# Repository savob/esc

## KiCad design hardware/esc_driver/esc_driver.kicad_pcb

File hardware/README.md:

# ESC Hardware Files

Here are the files related to the hardware design. They are all from KiCad 7.0.10 at the oldest.

## Projects

- `esc_vX` are different versions of the ESC
- `driver_ic_adapter` is a board I designed to act as an adapter so I could seat an IRS2334S chip on the footprint for a FAN7x88 chip
- `esc_driver` is a board just meant to hold the power stage of the ESC so one can connect it to different control circuits

## Other Files and Folders

- `esc.3dshapes` contains 3D models for custom footpints
- `esc.pretty` holds all the custom footprints needed by the ESC project
- `schematics` has the schematics in PDF (colour and B/W) and SVG (just colour) formats
- `esc_part.kicad_sym` holds the custom symbols used in the ESC project
- `small_title_block.kicad_wks` has the worksheet template with a more compact titleblock

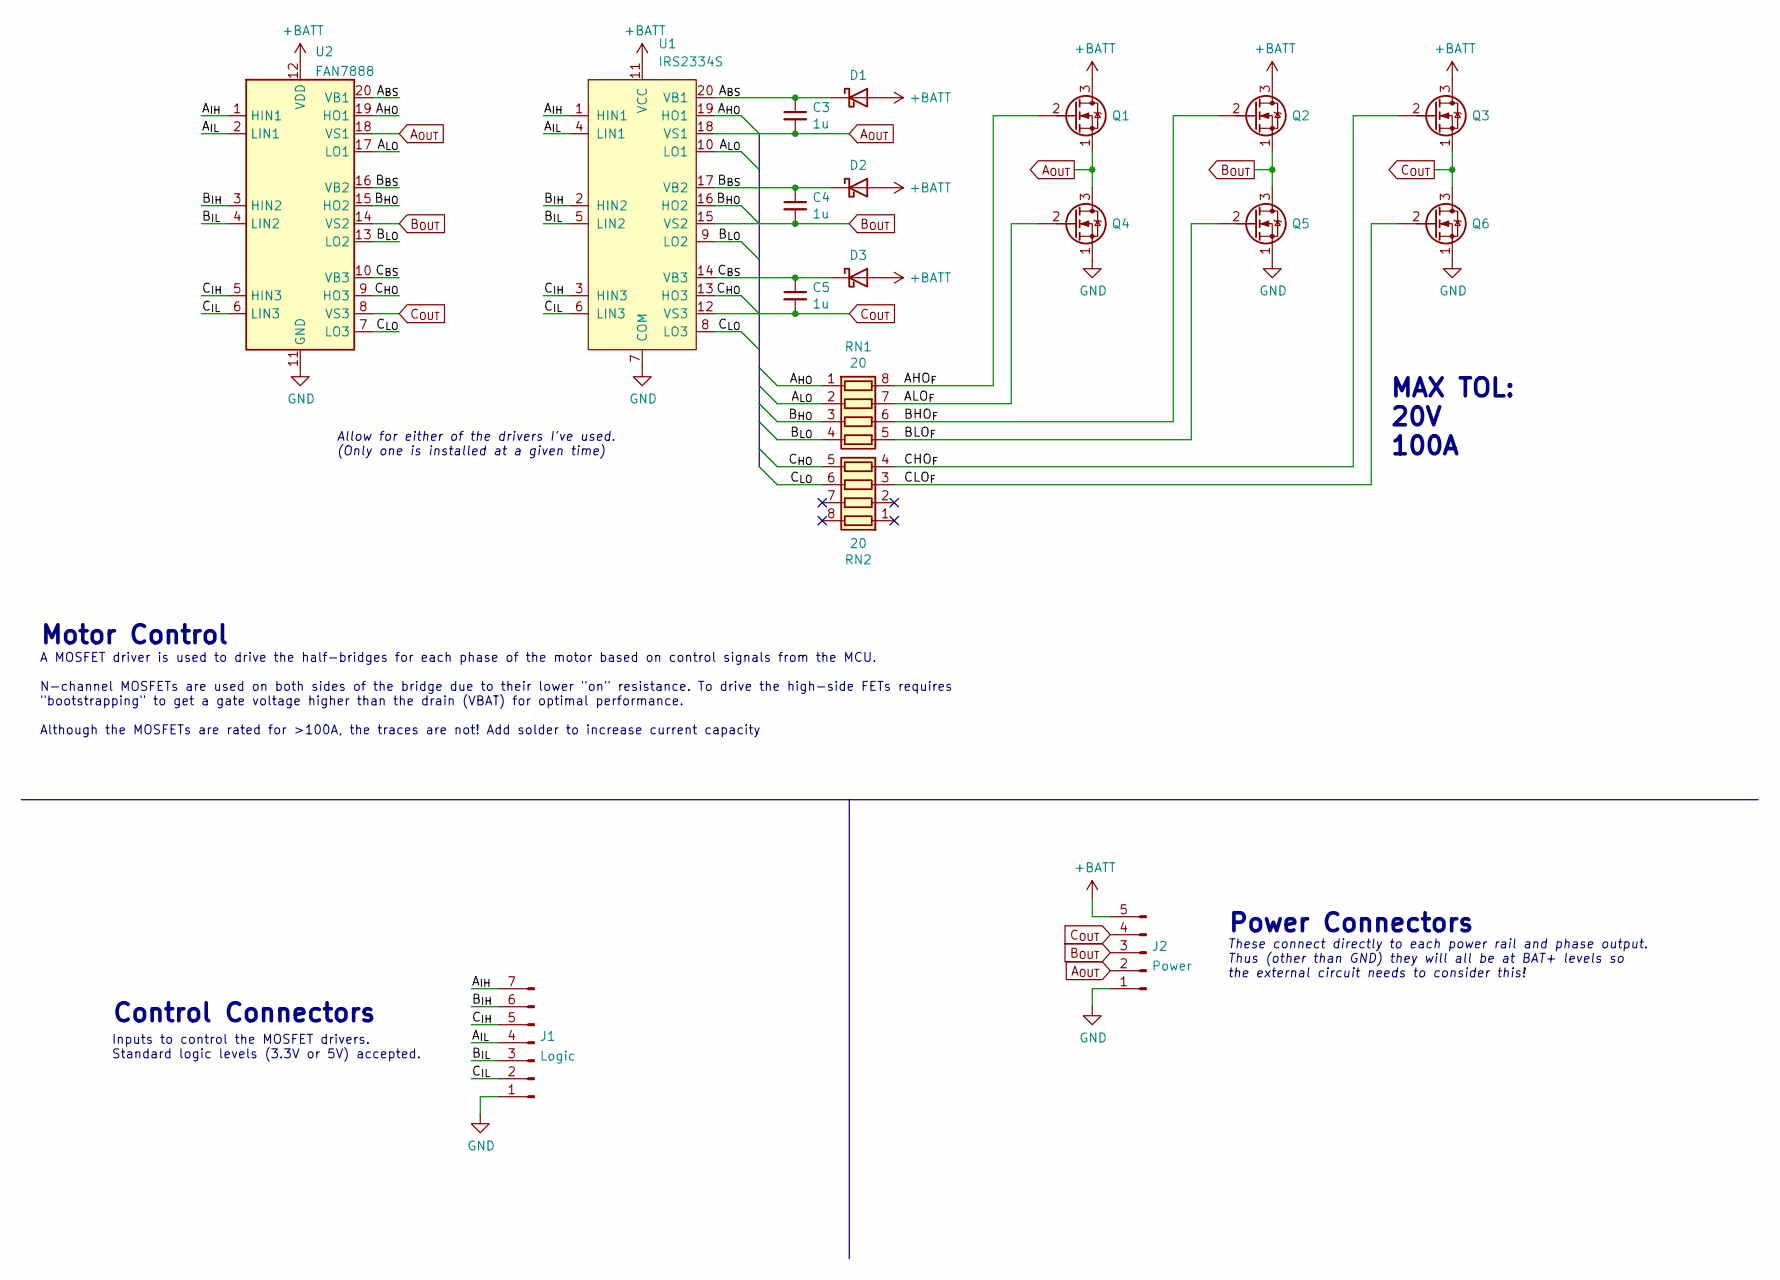
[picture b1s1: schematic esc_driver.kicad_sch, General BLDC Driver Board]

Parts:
C3, C4, C5: 1u; C_0603_1608Metric
D1, D2, D3: DSS15UTR; D_SOD-123F
J1: Logic; PinHeader_1x07_P2.54mm_Vertical
J2: Power; PinHeader_1x05_P2.54mm_Vertical
Q1, Q2, Q3, Q4, Q5, Q6: TPN2R903PL; TPN2R903PLL1Q
RN1, RN2: 20; R_Array_Convex_4x0603
U1: IRS2334S; SOIC-20W_7.5x12.8mm_P1.27mm
U2: FAN7888; SOIC-20W_7.5x12.8mm_P1.27mm

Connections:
+BATT: D1.2 (A), D2.2 (A), D3.2 (A), J2.5, Q1.3 (D), Q2.3 (D), Q3.3 (D), U1.11 (VCC), U2.12 (VDD)
/AHO_{F}: Q1.2 (G), RN1.8 (R1.2)
/ALO_{F}: Q4.2 (G), RN1.7 (R2.2)
/A_{BS}: C3.1, D1.1 (K), U1.20 (VB1), U2.20 (VB1)
/A_{HO}: RN1.1 (R1.1), U1.19 (HO1), U2.19 (HO1)
/A_{IH}: J1.7, U1.1 (HIN1), U2.1 (HIN1)
/A_{IL}: J1.4, U1.4 (LIN1), U2.2 (LIN1)
/A_{LO}: RN1.2 (R2.1), U1.10 (LO1), U2.17 (LO1)
/BHO_{F}: Q2.2 (G), RN1.6 (R3.2)
/BLO_{F}: Q5.2 (G), RN1.5 (R4.2)
/B_{BS}: C4.1, D2.1 (K), U1.17 (VB2), U2.16 (VB2)
/B_{HO}: RN1.3 (R3.1), U1.16 (HO2), U2.15 (HO2)
/B_{IH}: J1.6, U1.2 (HIN2), U2.3 (HIN2)
/B_{IL}: J1.3, U1.5 (LIN2), U2.4 (LIN2)
/B_{LO}: RN1.4 (R4.1), U1.9 (LO2), U2.13 (LO2)
/CHO_{F}: Q3.2 (G), RN2.4 (R4.1)
/CLO_{F}: Q6.2 (G), RN2.3 (R3.1)
/C_{BS}: C5.1, D3.1 (K), U1.14 (VB3), U2.10 (VB3)
/C_{HO}: RN2.5 (R4.2), U1.13 (HO3), U2.9 (HO3)
/C_{IH}: J1.5, U1.3 (HIN3), U2.5 (HIN3)
/C_{IL}: J1.2, U1.6 (LIN3), U2.6 (LIN3)
/C_{LO}: RN2.6 (R3.2), U1.8 (LO3), U2.7 (LO3)
A_{OUT}: C3.2, J2.2, Q1.1 (S), Q4.3 (D), U1.18 (VS1), U2.18 (VS1)
B_{OUT}: C4.2, J2.3, Q2.1 (S), Q5.3 (D), U1.15 (VS2), U2.14 (VS2)
C_{OUT}: C5.2, J2.4, Q3.1 (S), Q6.3 (D), U1.12 (VS3), U2.8 (VS3)
GND: J1.1, J2.1, Q4.1 (S), Q5.1 (S), Q6.1 (S), U1.7 (COM), U2.11 (GND)

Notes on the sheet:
A MOSFET driver is used to drive the half-bridges for each phase of the motor based on control signals from the MCU. N-channel MOSFETs are used on both sides of the bridge due to their lower "on" resistance. To drive the high-side FETs requires "bootstrapping" to get a gate voltage higher than the 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
These connect directly to each power rail and phase output. Thus (other than GND) they will all be at BAT+ levels so the external circuit needs to consider this!
Motor Control
Allow for either of the drivers I've used. (Only one is installed at a given time)
Power Connectors
MAX TOL: 20V 100A
Inputs to control the MOSFET drivers. Standard logic levels (3.3V or 5V) accepted.
Control Connectors

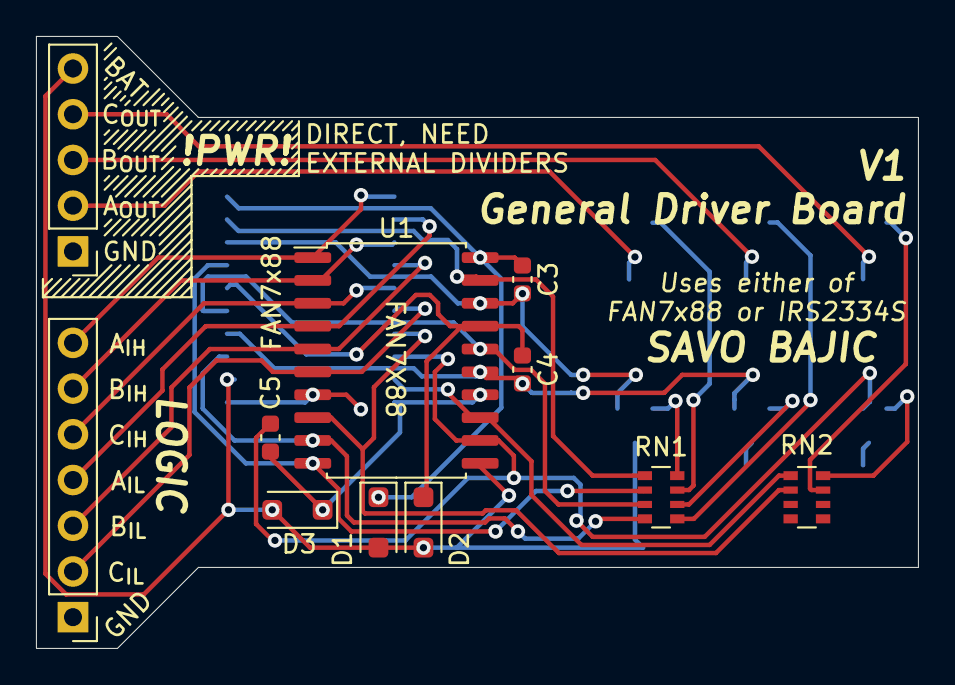
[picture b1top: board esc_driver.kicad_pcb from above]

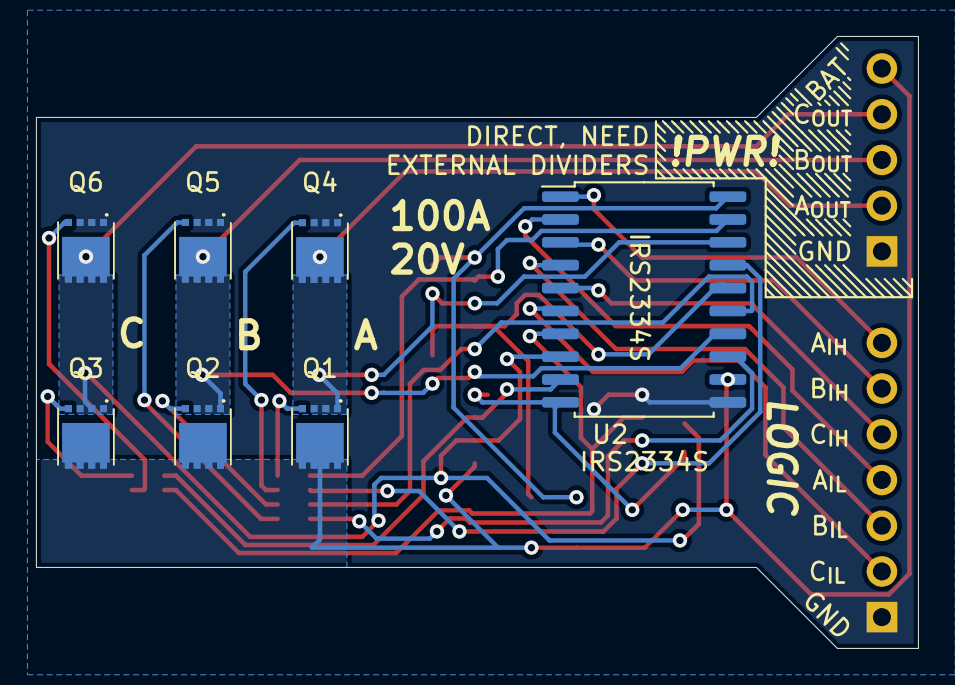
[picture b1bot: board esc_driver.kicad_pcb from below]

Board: 2 copper layers, 49.0 x 34.0 mm, 18 parts (7 on the bottom side), 26 nets.

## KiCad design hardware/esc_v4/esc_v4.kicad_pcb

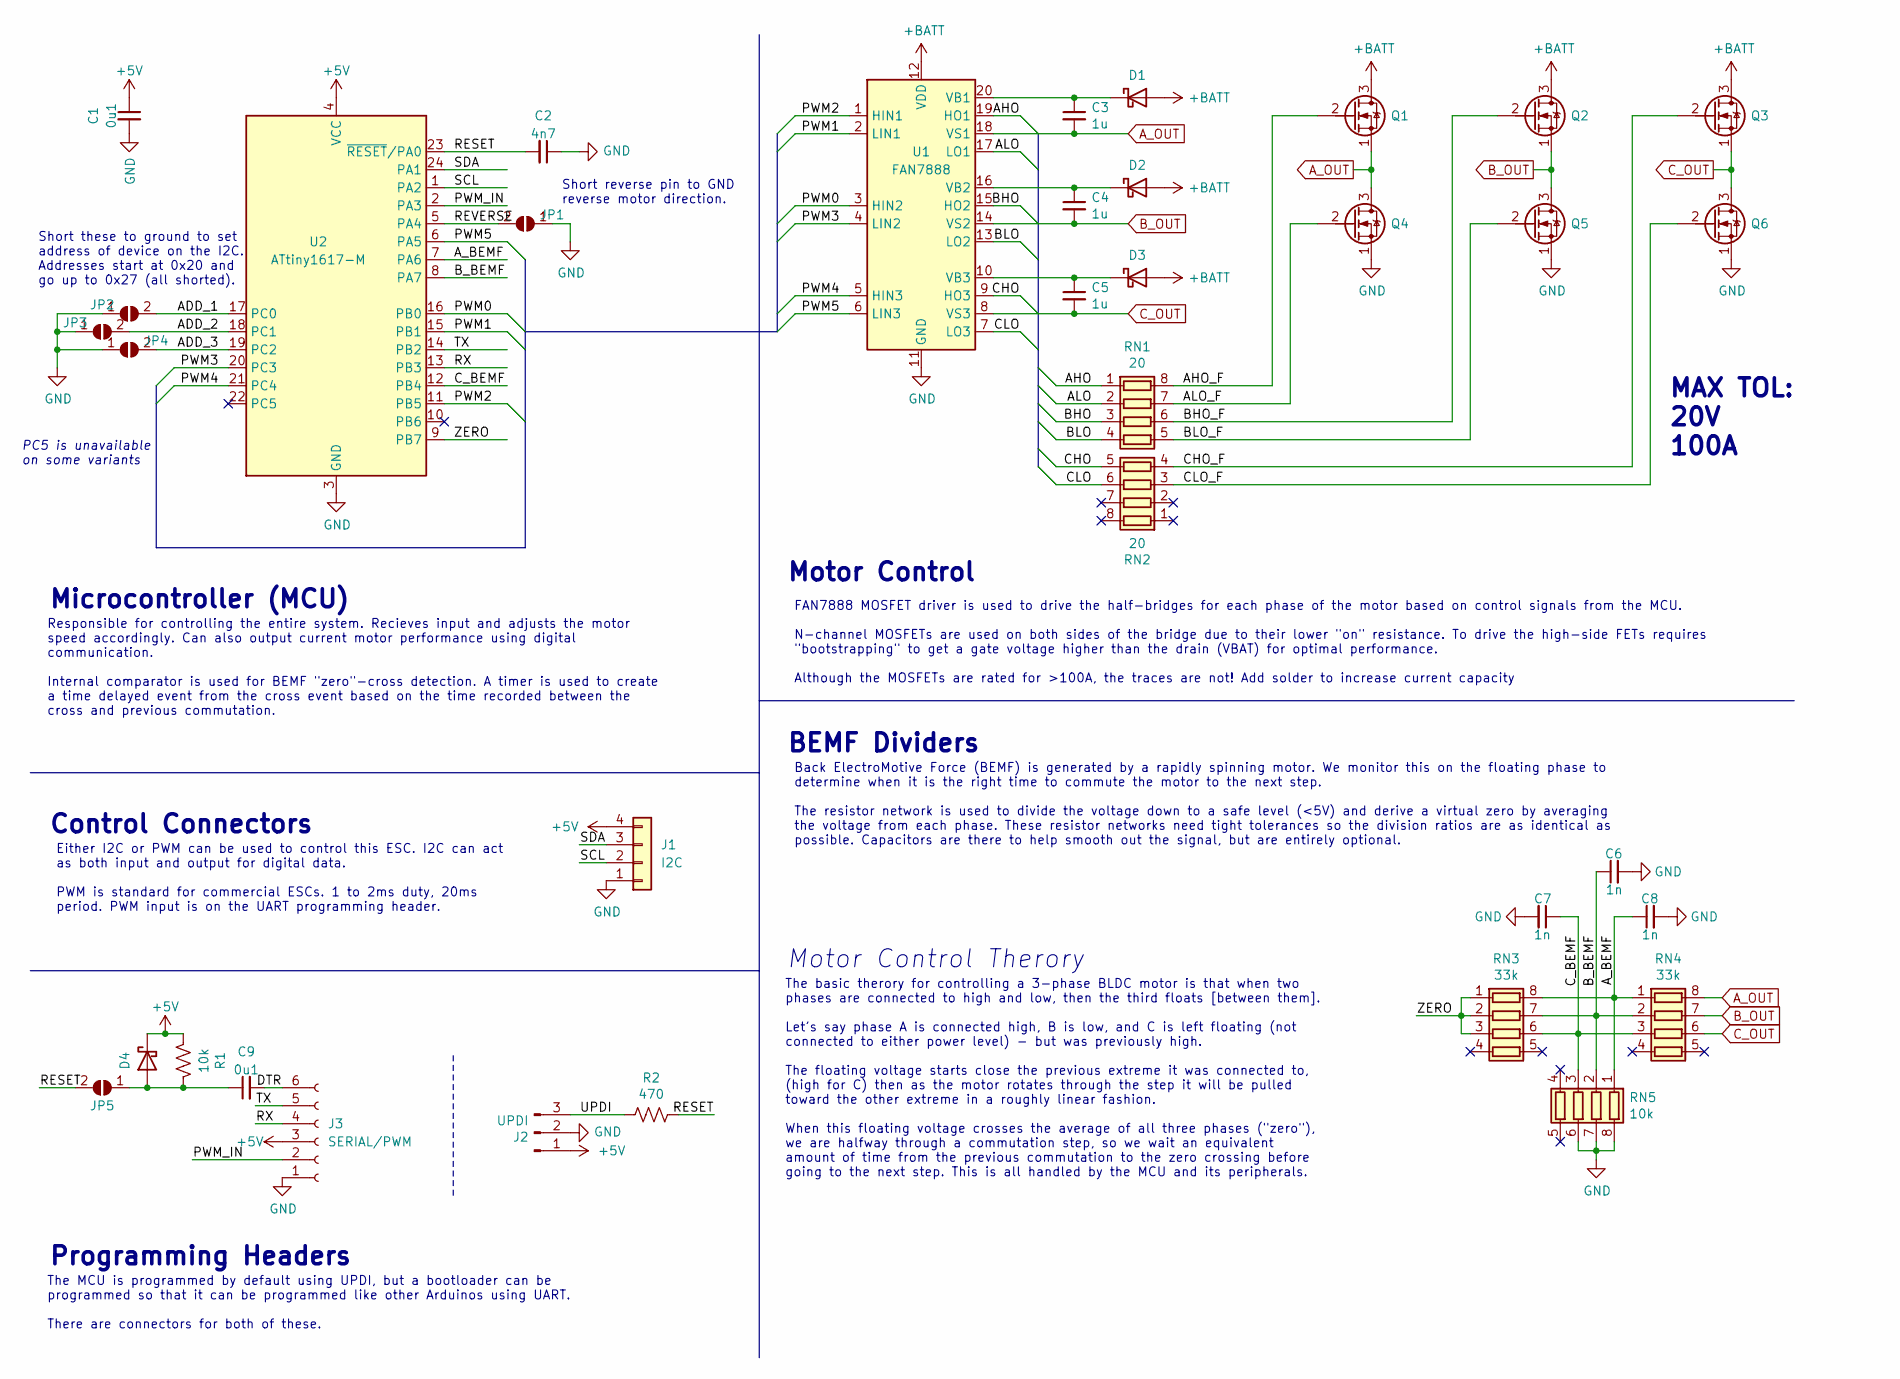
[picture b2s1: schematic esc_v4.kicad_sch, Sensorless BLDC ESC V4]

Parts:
C1, C9: 0u1; C_0402_1005Metric
C2: 4n7; C_0402_1005Metric
C3, C4, C5: 1u; C_0603_1608Metric
C6, C7, C8: 1n; C_0402_1005Metric
D1, D2, D3, D4: DSS15UTR; D_SOD-123F
J1: I2C; PinSocket_1x04_P2.54mm_Vertical
J2: UPDI; PinHeader_1x03_P2.54mm_Horizontal
J3: SERIAL/PWM; PinSocket_1x06_P2.54mm_Vertical
JP1, JP2, JP3, JP4: SolderJumper_2_Open; SolderJumper-2_P1.3mm_Open_TrianglePad1.0x1.5mm
JP5: SolderJumper_2_Open; SolderJumper-2_P1.3mm_Open_RoundedPad1.0x1.5mm
Q1, Q2, Q3, Q4, Q5, Q6: TPN2R903PL; TPN2R903PLL1Q
R1: 10k; R_0603_1608Metric
R2: 470; R_0603_1608Metric
RN1, RN2: 20; R_Array_Convex_4x0603
RN3, RN4: 33k; R_Array_Convex_4x0603
RN5: 10k; R_Cat16-4
U1: FAN7888; SOIC-20W_7.5x12.8mm_P1.27mm
U2: ATtiny1617-M; QFN-24-1EP_4x4mm_P0.5mm_EP2.6x2.6mm

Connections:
+5V: C1.1, D4.1 (K), J1.4, J2.1, J3.3, R1.1, U2.4 (VCC)
+BATT: D1.2 (A), D2.2 (A), D3.2 (A), Q1.3 (D), Q2.3 (D), Q3.3 (D), U1.12 (VDD)
/ADD_1: JP2.2 (B), U2.17 (PC0)
/ADD_2: JP3.2 (B), U2.18 (PC1)
/ADD_3: JP4.2 (B), U2.19 (PC2)
/AHO: RN1.1 (R1.1), U1.19 (HO1)
/AHO_F: Q1.2 (G), RN1.8 (R1.2)
/ALO: RN1.2 (R2.1), U1.17 (LO1)
/ALO_F: Q4.2 (G), RN1.7 (R2.2)
/A_BEMF: C8.1, RN3.8 (R1.2), RN4.1 (R1.1), RN5.1 (R1.1), U2.7 (PA6)
/BHO: RN1.3 (R3.1), U1.15 (HO2)
/BHO_F: Q2.2 (G), RN1.6 (R3.2)
/BLO: RN1.4 (R4.1), U1.13 (LO2)
/BLO_F: Q5.2 (G), RN1.5 (R4.2)
/B_BEMF: C6.1, RN3.7 (R2.2), RN4.2 (R2.1), RN5.2 (R2.1), U2.8 (PA7)
/CHO: RN2.5 (R4.2), U1.9 (HO3)
/CHO_F: Q3.2 (G), RN2.4 (R4.1)
/CLO: RN2.6 (R3.2), U1.7 (LO3)
/CLO_F: Q6.2 (G), RN2.3 (R3.1)
/C_BEMF: C7.1, RN3.6 (R3.2), RN4.3 (R3.1), RN5.3 (R3.1), U2.12 (PB4)
/DTR: C9.2, J3.6
/PWM0: U1.3 (HIN2), U2.16 (PB0)
/PWM1: U1.2 (LIN1), U2.15 (PB1)
/PWM2: U1.1 (HIN1), U2.11 (PB5)
/PWM3: U1.4 (LIN2), U2.20 (PC3)
/PWM4: U1.5 (HIN3), U2.21 (PC4)
/PWM5: U1.6 (LIN3), U2.6 (PA5)
/PWM_IN: J3.2, U2.2 (PA3)
/RESET: C2.2, JP5.2 (B), R2.1, U2.23 (~RESET/PA0)
/REVERSE: JP1.2 (B), U2.5 (PA4)
/RX: J3.4, U2.13 (PB3)
/SCL: J1.2, U2.1 (PA2)
/SDA: J1.3, U2.24 (PA1)
/TX: J3.5, U2.14 (PB2)
/UPDI: J2.3, R2.2
/ZERO: RN3.1 (R1.1), RN3.2 (R2.1), RN3.3 (R3.1), U2.9 (PB7)
A_OUT: C3.2, Q1.1 (S), Q4.3 (D), RN4.8 (R1.2), U1.18 (VS1)
B_OUT: C4.2, Q2.1 (S), Q5.3 (D), RN4.7 (R2.2), U1.14 (VS2)
C_OUT: C5.2, Q3.1 (S), Q6.3 (D), RN4.6 (R3.2), U1.8 (VS3)
GND: C1.2, C2.1, C6.2, C7.2, C8.2, J1.1, J2.2, J3.1, JP1.1 (A), JP2.1 (A), JP3.1 (A), JP4.1 (A), Q4.1 (S), Q5.1 (S), Q6.1 (S), RN5.6 (R3.2), RN5.7 (R2.2), RN5.8 (R1.2), U1.11 (GND), U2.3 (GND), U2.25 (GND)
unnamed: C3.1, D1.1 (K), U1.20 (VB1)
unnamed: C4.1, D2.1 (K), U1.16 (VB2)
unnamed: C5.1, D3.1 (K), U1.10 (VB3)
unnamed: C9.1, D4.2 (A), JP5.1 (A), R1.2

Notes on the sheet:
Back ElectroMotive Force (BEMF) is generated by a rapidly spinning motor. We monitor this on the floating phase to determine when it is the right time to commute the motor to the next step. The resistor network is used to divide the voltage down to a safe level (<5V) and derive a virtual zero by av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
The basic therory for controlling a 3-phase BLDC motor is that when two phases are connected to high and low, then the third floats [between them]. Let's say phase A is connected high, B is low, and C is left floating (not connected to either power level) - but was previously high. The floating vol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
FAN7888 MOSFET driver is used to drive the half-bridges for each phase of the motor based on control signals from the MCU. N-channel MOSFETs are used on both sides of the bridge due to their lower "on" resistance. To drive the high-side FETs requires "bootstrapping" to get a gate voltage higher tha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
Either I2C or PWM can be used to control this ESC. I2C can act as both input and output for digital data. PWM is standard for commercial ESCs. 1 to 2ms duty, 20ms period. PWM input is on the UART programming header.
The MCU is programmed by default using UPDI, but a bootloader can be programmed so that it can be programmed like other Arduinos using UART. There are connectors for both of these.
Responsible for controlling the entire system. Recieves input and adjusts the motor speed accordingly. Can also output current motor performance using digital communication. Internal comparator is used for BEMF "zero"-cross detection. A timer is used to create a time delayed event from the cross ev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
Short these to ground to set address of device on the I2C. Addresses start at 0x20 and go up to 0x27 (all shorted).
Microcontroller (MCU)
MAX TOL: 20V 100A
Motor Control Therory
PC5 is unavailable on some variants
Control Connectors
Programming Headers
Short reverse pin to GND reverse motor direction.
Motor Control
BEMF Dividers

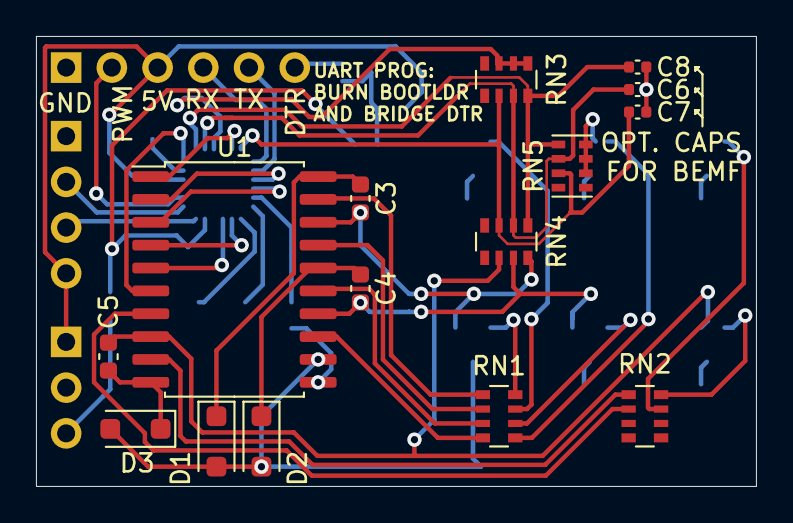
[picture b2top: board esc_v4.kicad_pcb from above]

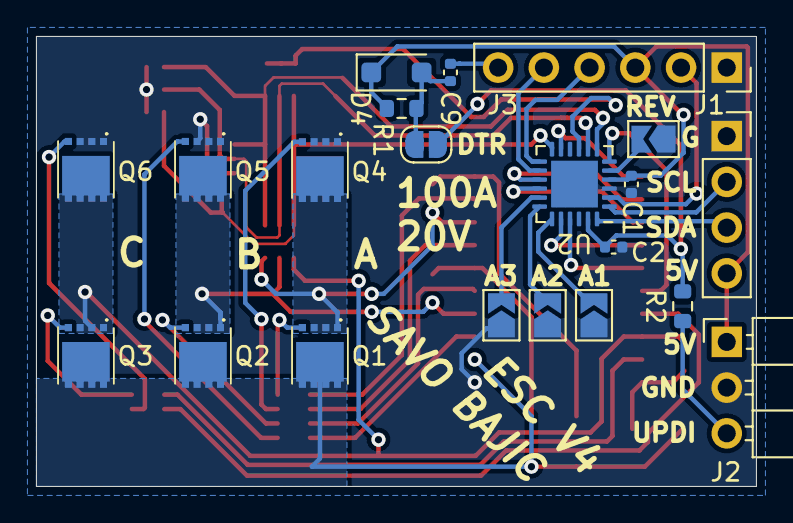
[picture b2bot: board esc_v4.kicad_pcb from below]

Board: 2 copper layers, 40.0 x 25.0 mm, 36 parts (21 on the bottom side), 44 nets.

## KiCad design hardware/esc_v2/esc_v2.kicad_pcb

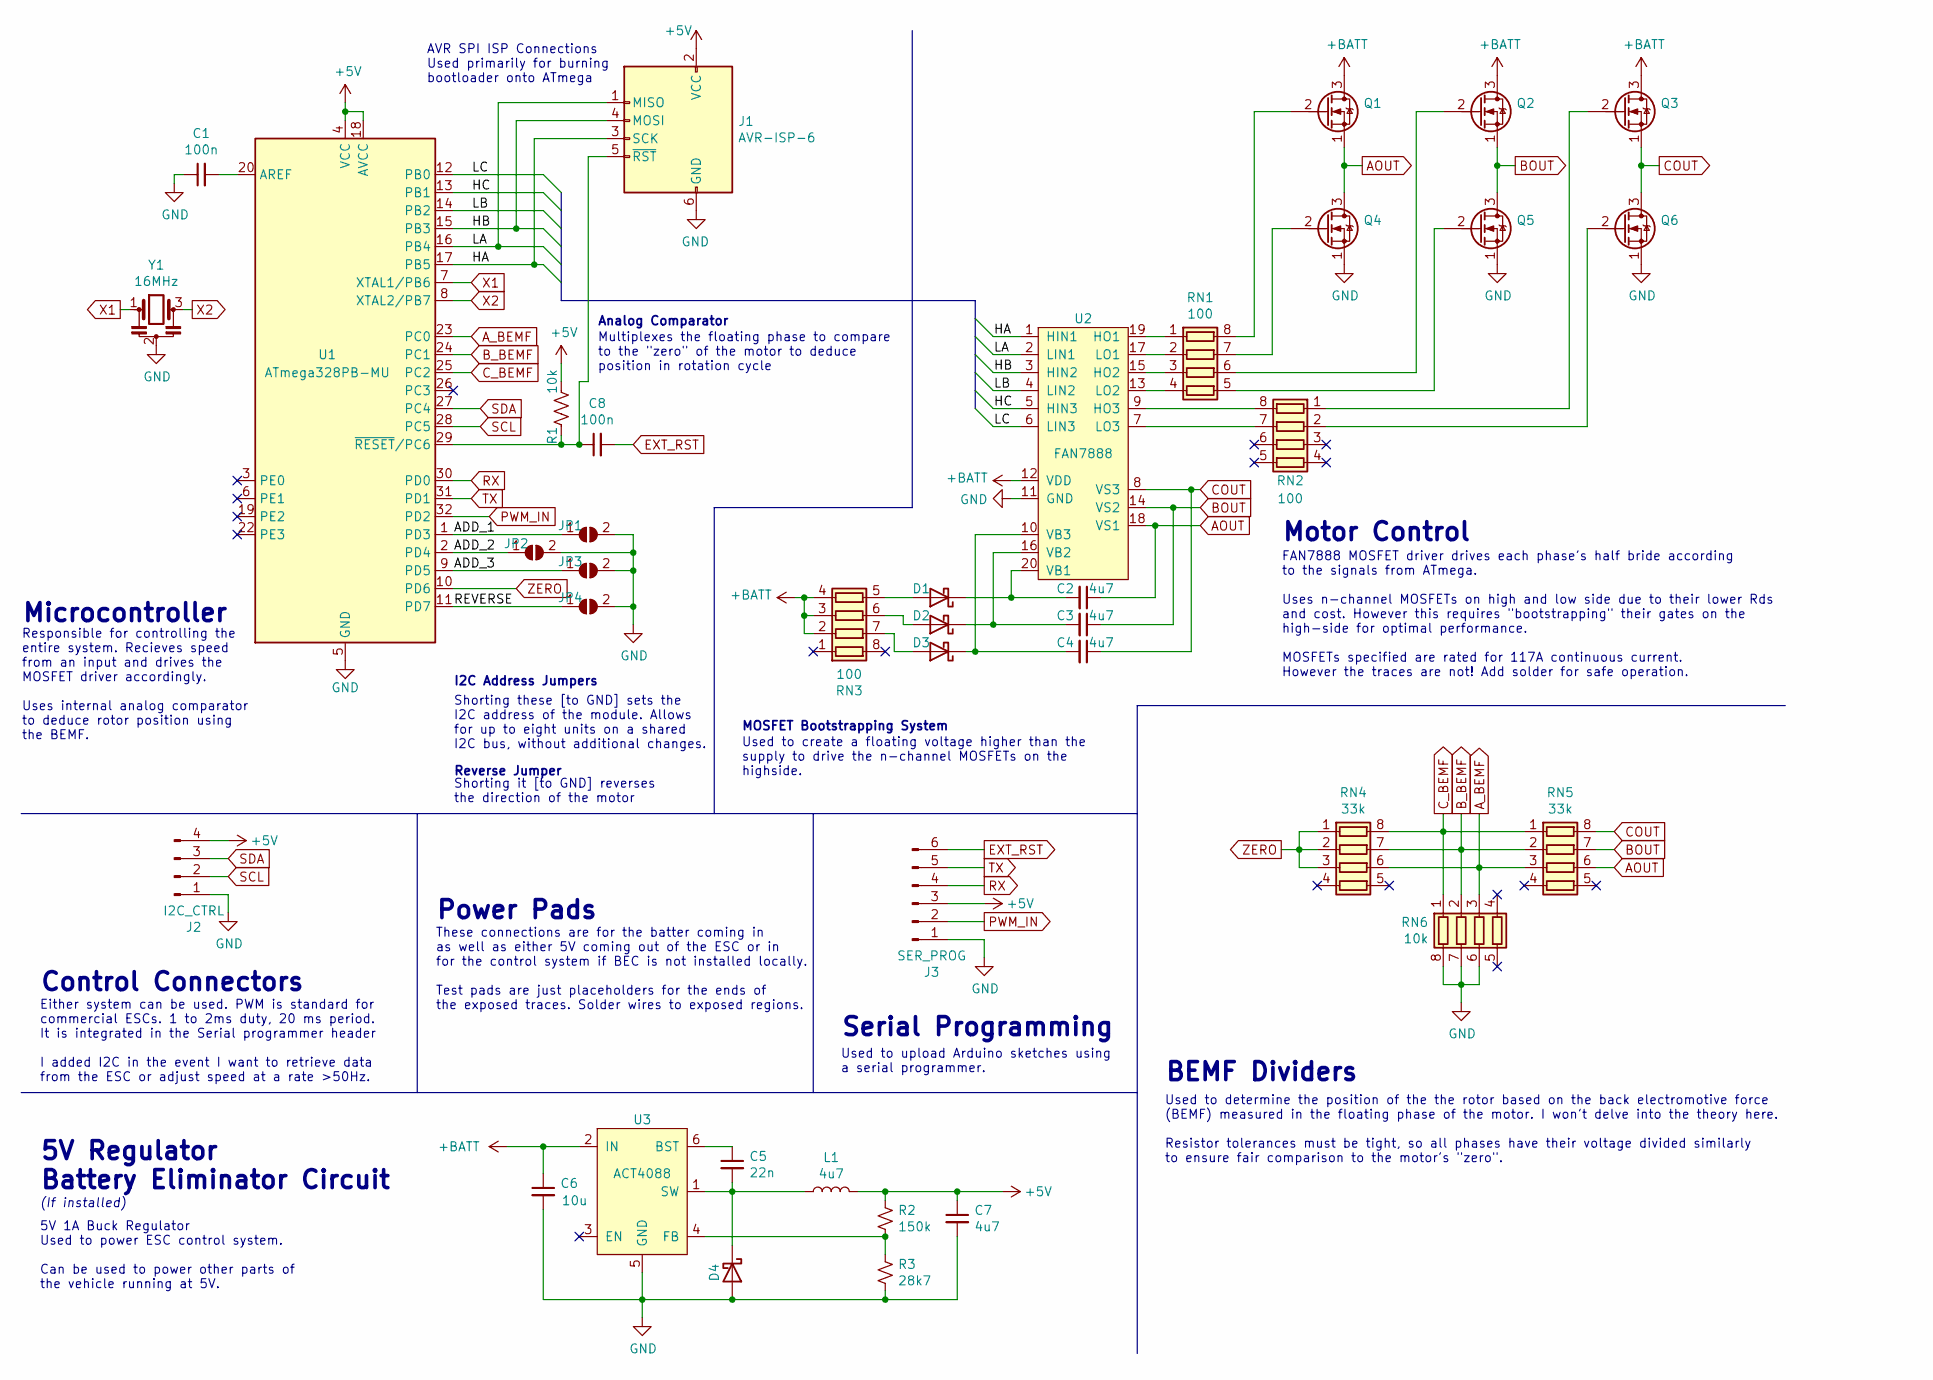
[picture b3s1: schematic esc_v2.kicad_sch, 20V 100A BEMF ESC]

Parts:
C1, C8: 100n; C_0402_1005Metric
C2, C3, C4, C7: 4u7; C_0805_2012Metric
C5: 22n; C_0402_1005Metric
C6: 10u; C_0805_2012Metric
D1, D2, D3, D4: 0v8; D_SOD-323
J1: AVR-ISP-6; PinHeader_2x03_P2.54mm_Vertical_SMD
J2: I2C_CTRL; PinHeader_1x04_P2.54mm_Vertical
J3: SER_PROG; PinSocket_1x06_P2.54mm_Vertical
JP1: A1; SolderJumper-2_P1.3mm_Open_TrianglePad1.0x1.5mm
JP2: A2; SolderJumper-2_P1.3mm_Open_TrianglePad1.0x1.5mm
JP3: A3; SolderJumper-2_P1.3mm_Open_TrianglePad1.0x1.5mm
JP4: REV; SolderJumper-2_P1.3mm_Open_TrianglePad1.0x1.5mm
L1: 4u7; L_Taiyo-Yuden_NR-30xx
Q1, Q2, Q3, Q4, Q5, Q6: Q_NMOS_SGD; TPN2R903PLL1Q
R1: 10k; R_0402_1005Metric
R2: 150k; R_0402_1005Metric
R3: 28k7; R_0402_1005Metric
RN1, RN2, RN3: 100; R_Array_Convex_4x0402
RN4, RN5: 33k; R_Array_Convex_4x0402
RN6: 10k; R_Array_Convex_4x0402
U1: ATmega328PB-MU; QFN-32-1EP_5x5mm_P0.5mm_EP3.1x3.1mm
U2: FAN7888; SOIC-20W_7.5x12.8mm_P1.27mm
U3: ACT4088; SOT-23-6
Y1: 16MHz; Resonator_SMD_muRata_CSTxExxV-3Pin_3.0x1.1mm

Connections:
+5V: C7.1, J1.2 (VCC), J2.4, J3.3, L1.2, R1.1, R2.2, U1.4 (VCC), U1.18 (AVCC)
+BATT: C6.1, Q1.3 (D), Q2.3 (D), Q3.3 (D), RN3.2 (R2.1), RN3.3 (R3.1), RN3.4 (R4.1), U2.12 (VDD), U3.2 (IN)
/ADD_1: JP1.1 (A), U1.1 (PD3)
/ADD_2: JP2.1 (A), U1.2 (PD4)
/ADD_3: JP3.1 (A), U1.9 (PD5)
/HA: J1.3 (SCK), U1.17 (PB5), U2.1 (HIN1)
/HB: J1.4 (MOSI), U1.15 (PB3), U2.3 (HIN2)
/HC: U1.13 (PB1), U2.5 (HIN3)
/LA: J1.1 (MISO), U1.16 (PB4), U2.2 (LIN1)
/LB: U1.14 (PB2), U2.4 (LIN2)
/LC: U1.12 (PB0), U2.6 (LIN3)
/REVERSE: JP4.1 (A), U1.11 (PD7)
AOUT: C2.1, Q1.1 (S), Q4.3 (D), RN5.6 (R3.2), U2.18 (VS1)
A_BEMF: RN4.6 (R3.2), RN5.3 (R3.1), RN6.3 (R3.1), U1.23 (PC0)
BOUT: C3.1, Q2.1 (S), Q5.3 (D), RN5.7 (R2.2), U2.14 (VS2)
B_BEMF: RN4.7 (R2.2), RN5.2 (R2.1), RN6.2 (R2.1), U1.24 (PC1)
COUT: C4.1, Q3.1 (S), Q6.3 (D), RN5.8 (R1.2), U2.8 (VS3)
C_BEMF: RN4.8 (R1.2), RN5.1 (R1.1), RN6.1 (R1.1), U1.25 (PC2)
EXT_RST: C8.2, J3.6
GND: C1.1, C6.2, C7.2, D4.2 (A), J1.6 (GND), J2.1, J3.1, JP1.2 (B), JP2.2 (B), JP3.2 (B), JP4.2 (B), Q4.1 (S), Q5.1 (S), Q6.1 (S), R3.1, RN6.6 (R3.2), RN6.7 (R2.2), RN6.8 (R1.2), U1.5 (GND), U1.21 (GND), U1.33 (GND), U2.11 (GND), U3.5 (GND), Y1.2
unnamed: D1.2 (A), RN3.5 (R4.2)
unnamed: C2.2, D1.1 (K), U2.20 (VB1)
unnamed: D2.2 (A), RN3.6 (R3.2)
unnamed: C3.2, D2.1 (K), U2.16 (VB2)
unnamed: D3.2 (A), RN3.7 (R2.2)
unnamed: C4.2, D3.1 (K), U2.10 (VB3)
unnamed: C5.2, D4.1 (K), L1.1, U3.1 (SW)
unnamed: C8.1, J1.5 (~RST), R1.2, U1.29 (~RESET/PC6)
unnamed: Q1.2 (G), RN1.8 (R1.2)
unnamed: Q2.2 (G), RN1.6 (R3.2)
unnamed: Q3.2 (G), RN2.1 (R1.1)
unnamed: Q4.2 (G), RN1.7 (R2.2)
unnamed: Q5.2 (G), RN1.5 (R4.2)
unnamed: Q6.2 (G), RN2.2 (R2.1)
unnamed: RN1.1 (R1.1), U2.19 (HO1)
unnamed: RN1.2 (R2.1), U2.17 (LO1)
unnamed: RN1.3 (R3.1), U2.15 (HO2)
unnamed: RN1.4 (R4.1), U2.13 (LO2)
unnamed: RN2.8 (R1.2), U2.9 (HO3)
unnamed: RN2.7 (R2.2), U2.7 (LO3)
unnamed: C1.2, U1.20 (AREF)
unnamed: C5.1, U3.6 (BST)
unnamed: R2.1, R3.2, U3.4 (FB)
PWM_IN: J3.2, U1.32 (PD2)
RX: J3.4, U1.30 (PD0)
SCL: J2.2, U1.28 (PC5)
SDA: J2.3, U1.27 (PC4)
TX: J3.5, U1.31 (PD1)
X1: U1.7 (XTAL1/PB6), Y1.1
X2: U1.8 (XTAL2/PB7), Y1.3
ZERO: RN4.1 (R1.1), RN4.2 (R2.1), RN4.3 (R3.1), U1.10 (PD6)

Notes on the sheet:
Serial Programming
5V 1A Buck Regulator Used to power ESC control system. Can be used to power other parts of the vehicle running at 5V.
AVR SPI ISP Connections Used primarily for burning bootloader onto ATmega
BEMF Dividers
Analog Comparator
Used to upload Arduino sketches using a serial programmer.
Shorting it [to GND] reverses the direction of the motor
Reverse Jumper
Shorting these [to GND] sets the I2C address of the module. Allows for up to eight units on a shared I2C bus, without additional changes.
These connections are for the batter coming in as well as either 5V coming out of the ESC or in for the control system if BEC is not installed locally. Test pads are just placeholders for the ends of the exposed traces. Solder wires to exposed regions.
Responsible for controlling the entire system. Recieves speed from an input and drives the MOSFET driver accordingly. Uses internal analog comparator to deduce rotor position using the BEMF.
Used to determine the position of the the rotor based on the back electromotive force (BEMF) measured in the floating phase of the motor. I won't delve into the theory here. Resistor tolerances must be tight, so all phases have their voltage divided similarly to ensure fair comparison to the motor'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
Control Connectors
Microcontroller
(If installed)
FAN7888 MOSFET driver drives each phase's half bride according to the signals from ATmega. Uses n-channel MOSFETs on high and low side due to their lower Rds and cost. However this requires "bootstrapping" their gates on the high-side for optimal performance. MOSFETs specified are rated for 117A co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
Either system can be used. PWM is standard for commercial ESCs. 1 to 2ms duty, 20 ms period. It is integrated in the Serial programmer header I added I2C in the event I want to retrieve data from the ESC or adjust speed at a rate >50Hz.
Used to create a floating voltage higher than the supply to drive the n-channel MOSFETs on the highside.
Motor Control
5V Regulator Battery Eliminator Circuit
I2C Address Jumpers
MOSFET Bootstrapping System
Power Pads
Multiplexes the floating phase to compare to the "zero" of the motor to deduce position in rotation cycle

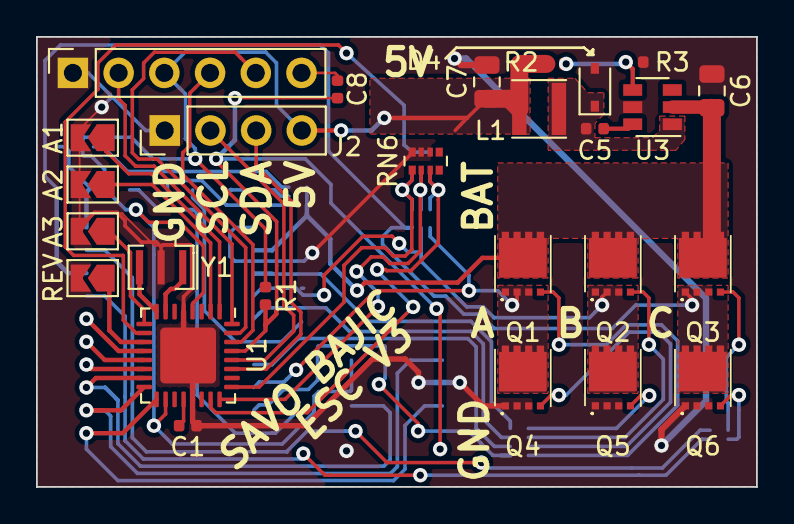
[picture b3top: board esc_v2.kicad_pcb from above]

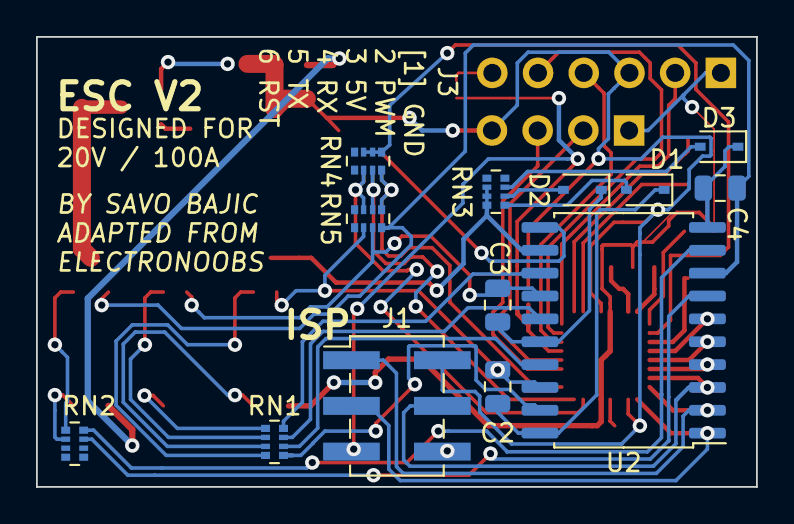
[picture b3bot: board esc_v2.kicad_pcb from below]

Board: 2 copper layers, 40.0 x 25.0 mm, 39 parts (13 on the bottom side), 51 nets.

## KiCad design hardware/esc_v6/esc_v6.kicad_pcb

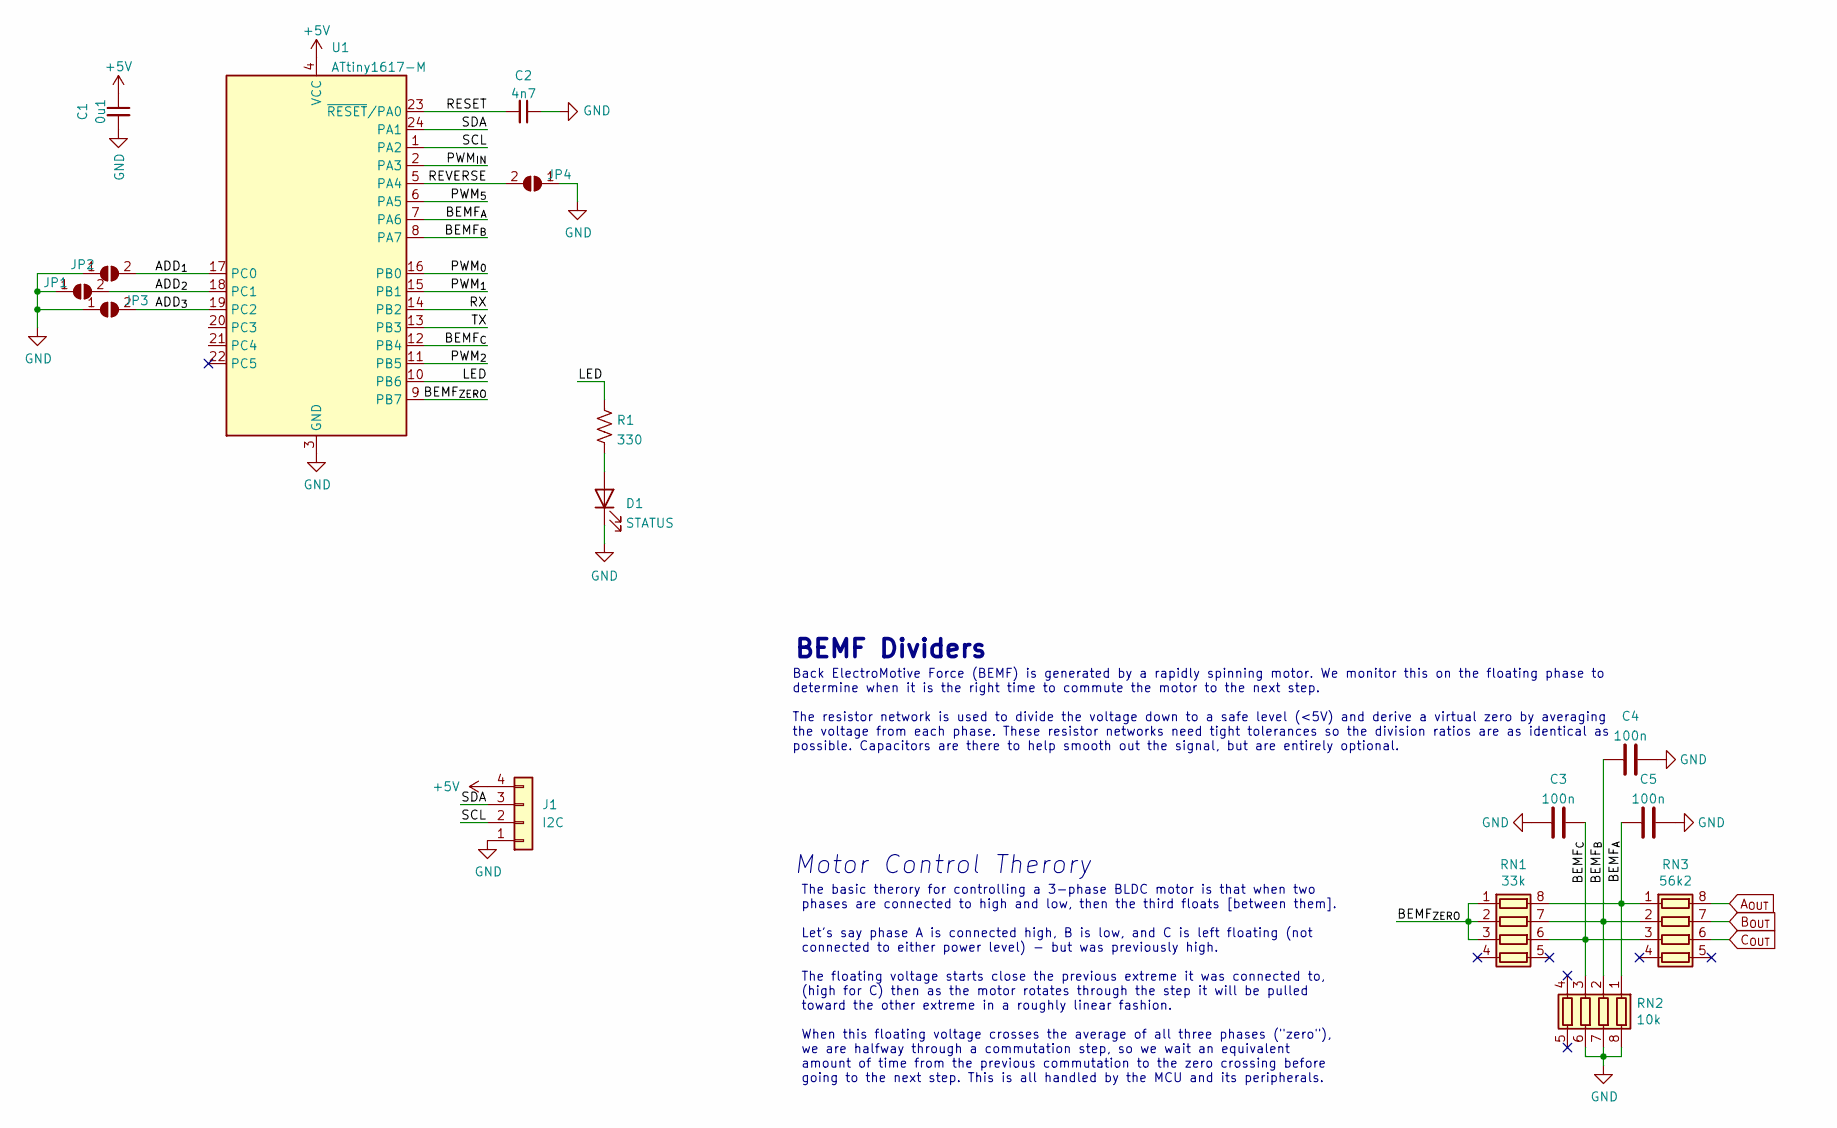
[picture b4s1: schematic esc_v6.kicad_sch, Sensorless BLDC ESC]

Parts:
C1: 0u1; C_0603_1608Metric
C2: 4n7; C_0603_1608Metric
C3, C4, C5: 100n; C_0603_1608Metric
D1: STATUS; LED_0805_2012Metric
J1: I2C; PinSocket_1x04_P2.54mm_Vertical
JP1, JP2, JP3, JP4: SolderJumper_2_Open; SolderJumper-2_P1.3mm_Open_TrianglePad1.0x1.5mm
R1: 330; R_0603_1608Metric
RN1: 33k; R_Array_Convex_4x0603
RN2: 10k; R_Cat16-4
RN3: 56k2; R_Array_Convex_4x0603
U1: ATtiny1617-M; QFN-24-1EP_4x4mm_P0.5mm_EP2.6x2.6mm

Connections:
+5V: C1.1, J1.4, U1.4 (VCC)
/ADD_{1}: JP2.2 (B), U1.17 (PC0)
/ADD_{2}: JP1.2 (B), U1.18 (PC1)
/ADD_{3}: JP3.2 (B), U1.19 (PC2)
/BEMF_{A}: C5.2, RN1.8 (R1.2), RN2.1 (R1.1), RN3.1 (R1.1), U1.7 (PA6)
/BEMF_{B}: C4.1, RN1.7 (R2.2), RN2.2 (R2.1), RN3.2 (R2.1), U1.8 (PA7)
/BEMF_{C}: C3.2, RN1.6 (R3.2), RN2.3 (R3.1), RN3.3 (R3.1), U1.12 (PB4)
/BEMF_{ZERO}: RN1.1 (R1.1), RN1.2 (R2.1), RN1.3 (R3.1), U1.9 (PB7)
/LED: R1.1, U1.10 (PB6)
/PWM_{0}: U1.16 (PB0)
/PWM_{1}: U1.15 (PB1)
/PWM_{2}: U1.11 (PB5)
/PWM_{3}: U1.20 (PC3)
/PWM_{4}: U1.21 (PC4)
/PWM_{5}: U1.6 (PA5)
/PWM_{IN}: U1.2 (PA3)
/RESET: C2.2, U1.23 (~RESET/PA0)
/REVERSE: JP4.2 (B), U1.5 (PA4)
/RX: U1.14 (PB2)
/SCL: J1.2, U1.1 (PA2)
/SDA: J1.3, U1.24 (PA1)
/TX: U1.13 (PB3)
A_{OUT}: RN3.8 (R1.2)
B_{OUT}: RN3.7 (R2.2)
C_{OUT}: RN3.6 (R3.2)
GND: C1.2, C2.1, C3.1, C4.2, C5.1, D1.1 (K), J1.1, JP1.1 (A), JP2.1 (A), JP3.1 (A), JP4.1 (A), RN2.6 (R3.2), RN2.7 (R2.2), RN2.8 (R1.2), U1.3 (GND), U1.25 (GND)
unnamed: D1.2 (A), R1.2

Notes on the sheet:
Back ElectroMotive Force (BEMF) is generated by a rapidly spinning motor. We monitor this on the floating phase to determine when it is the right time to commute the motor to the next step. The resistor network is used to divide the voltage down to a safe level (<5V) and derive a virtual zero by av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
The basic therory for controlling a 3-phase BLDC motor is that when two phases are connected to high and low, then the third floats [between them]. Let's say phase A is connected high, B is low, and C is left floating (not connected to either power level) - but was previously high. The floating vol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
BEMF Dividers
Motor Control Therory

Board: 4 copper layers, 16 parts (0 on the bottom side), 15 nets, no tracks yet.

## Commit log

2024-01-04 Uploaded hardware files
2024-01-04 Added `hardware` readme
2024-01-04 Uploading early (Arduino IDE) ESC code
2024-01-04 Added licence
